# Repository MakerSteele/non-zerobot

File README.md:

# Non-Zerobot

A small 3D-printed FPV robot you drive from your phone's web browser. It streams live video, has RGB headlights, keeps itself driving straight using wheel encoders, and can even *talk* through its drive motors.

It started life as a Raspberry Pi Zero robot — hence the name. Pi Zeros got hard to find, so it now runs happily on a Pi 3B+ too. It's kind of a non-zero bot now.

> **Built on the shoulders of others.** This project is based on Max Kern's **ZeroBot** and **ZeroBot Pro**, and ZDV's **ZeroBot Pro V1** remix. See [CREDITS.md](CREDITS.md).

> 🚧 **Work in progress.** The software works today. The printable parts are in [`models/`](models/). The carrier board on the robot today (Rev F) is in [`hardware/carrier-rev-f/`](hardware/carrier-rev-f/) for reference. It has known faults, so don't order it; the fixed Rev G board will be added once it has been built and tested. Hold off on ordering parts for now.

**Building one?** Go in this order: [parts list](BOM.md) → [assemble it](ASSEMBLY.md) → [install the software](INSTALL.md). Already have a robot? Jump straight to **[INSTALL.md](INSTALL.md)**.

---

## What it does

- **Drive from any phone** — Android or iPhone, nothing to install. Just open a web page.
- **Live video** from the Pi camera, with photo and video recording. **HD VIEW** switches the live picture to full HD for a sharper view or close-up work (more Wi-Fi load while it's on; tested on a Pi 3B+ with the Camera Module 3).
- **RGB headlights** with colour and brightness control.
- **Drives straight on its own** — the encoder motors let it balance left and right wheel speed automatically.
- **Talks through its motors** — hold **TALK** and speak into your phone, or type a sentence under ⚙ → **SOUNDS**, and the robot says it out loud by buzzing its drive motors like a speaker.
- **Built-in self-checks** — buttons to confirm motors and encoders are wired the right way round.
- **Looks after itself** — runs as a background service, restarts if it ever hangs, and shuts down safely on low battery.

## Supported hardware

| Part | Options |
|---|---|
| **Raspberry Pi** | Pi 3B+ (main build), Pi 3B, Pi 3A+, Pi Zero 2 W, Pi Zero W |
| **Camera** | Camera Module 3, OV5647 (cheaper), or the Pi AI Camera (used as a regular camera) |
| **Motors** | Hiwonder geared motors with hall-effect encoders |
| **Motor driver** | TB6612FNG board |
| **Battery** | Two 18650 cells in parallel, with a charger/5 V boost board for the Pi and a 6 V boost for the motors |
| **Battery meter** | ADS1115 ADC board |
| **Headlights** | 10 mm common-anode RGB LEDs |

A carrier circuit board that ties all of this together is in progress and will be added here once the current revision is proven.

## How it got here

| Pi Zero W | Pi Zero 2 W | Out for a drive |
|---|---|---|
|  |  |  |

## Getting started

- 🧾 **[BOM.md](BOM.md)**: every part, with part numbers and a DigiKey order list
- 🔧 **[ASSEMBLY.md](ASSEMBLY.md)**: build the robot step by step (🚧 in progress, not yet tested on a real build)
- 📘 **[Visual assembly manual (PDF)](docs/NonZerobot_Assembly_Manual.pdf)**: the printed chassis put together, step by step, with pictures (🚧 in progress)
- 💾 **[INSTALL.md](INSTALL.md)**: install the software. No Linux experience needed
- 📦 **[Releases](https://github.com/MakerSteele/non-zerobot/releases)**: download just the robot software (`zerobot.zip`)

## Wiring (GPIO, BCM numbering)

| Function | GPIO |
|---|---|
| Left motor forward / backward | 17 / 27 |
| Right motor forward / backward | 22 / 23 |
| Encoders | 5, 13 (6, 19 wired for future use) |
| White headlight | 24 |
| RGB headlight red / green / blue | 12 / 16 / 26 |
| ADS1115 battery sense | I2C (GPIO 2 / 3) |

## Repo layout

```
zerobot/     the robot software - this whole folder goes on the Pi as ~/zerobot
docs/bom/    DigiKey order list and a kit cost calculator
docs/images/ photos
docs/        visual assembly manual (PDF)
models/      3D-printable parts (STL); models/rev-g/ = parts for the Rev G carrier
hardware/    carrier board files (Rev F, for reference: see its known issues)
```

## License

- **Software** (everything in `zerobot/`): [GPL-3.0](LICENSE)
- **Documentation and images**: [CC BY-SA 4.0](LICENSE-DOCS.md)
- **3D models** (everything in `models/`): [CC BY-NC-SA 4.0](models/LICENSE.md) — non-commercial, because the chassis is a remix of ZDV's CC BY-NC-SA design

Found a problem or have an idea? [Open an issue](https://github.com/MakerSteele/non-zerobot/issues).

Follow the build series: **@MakerSteele** on Instagram and TikTok.

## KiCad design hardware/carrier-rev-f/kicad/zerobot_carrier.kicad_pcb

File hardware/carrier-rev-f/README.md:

# Carrier board, Rev F (the board on the robot today)

This is the carrier board the original Non-Zerobot drives on. It's here so you can see exactly what's in the robot.

> ⚠️ **Don't order this board as it is.** It has two wiring faults (below). The robot only works because of hand fixes. **Rev G** fixes both, and its files will be added once a Rev G board has been built and tested.

## Files

| File | What it is |
|---|---|
| `zipme/` | Gerbers for JLCPCB (2 layers, 1.6 mm). **Zip the files inside this folder** and upload that zip |
| `kicad/` | KiCad project (made in KiCad 7; newer versions upgrade it) |
| `zerobot_carrier.step` | 3D model for CAD |
| `zerobot_carrier_schematic.pdf` | Schematic |
| `zerobot_carrier_1to1_fitcheck.pdf` | Print at 100 % and lay the modules on it |
| `scripts/` | The scripts that generate the board |

## Known issues

### 1. Boost footprints are mirrored (both boosts)
The two SX1308 boost footprints ("PI BOOST 5.1V" and "MOTOR BOOST 6.0V") were drawn from the board's label side, so they come out as mirror images. With a boost fitted parts-side up, the battery lands on the boost's **output** pin and nothing reaches its input, so the Pi gets no power.

**Fix on the original robot:**
- **Pi rail:** the Pi boost is removed. The 5 V output of the charger/boost combo board in the shell feeds the Pi side of the **Pi power jumper (JP1)**, with − to the carrier's battery − pad. This skips the rocker switch and the fuse, so pulling JP1 is the Pi's on/off.
- **Motor rail:** a boost set to 6.0 V, wired by hand to match its real pins. Running the motors straight off the battery also works (bridge the battery to the motor side of the **motor power jumper, JP2**), but they're noticeably weaker.

### 2. Motor sockets are reversed
The Hiwonder encoder-motor plug (G, H1, H2, V, M+, M−) lands end-for-end in the left and right motor sockets. With the plug in, the motor driver's output hits the encoder pins and the Pi's 3.3 V hits the motor. The motors don't turn, and **an encoder can be damaged**.

**Fix:** reverse the wire order inside both motor plugs (lift each crimp out of the housing and re-insert it at the other end) before plugging them in.

### 3. Battery + label is misleading
The **+** for the battery is printed nearest the ground pad, and the charger pads have no label. **+ is the square pad** on both.

### 4. Front mounting holes
The front pair of mounting holes sits over the battery-spring install holes. The main lower shell in [`models/`](../../models/) has its standoffs here, so it fits this board. Rev G moves these holes; its lower shell is in [`models/rev-g/`](../../models/rev-g/).

## Tip
The TB6612 motor-driver module goes in one way only: its **PWMA** pin row toward the front (headlight end), its **VM** row toward the rear, with PWMA and VM at the left (Pi-header) end. Fitted the other way round, it shorts the Pi's 3.3 V rail.

## License
Board files are shared under [CC BY-SA 4.0](../../LICENSE-DOCS.md), the same as the docs.

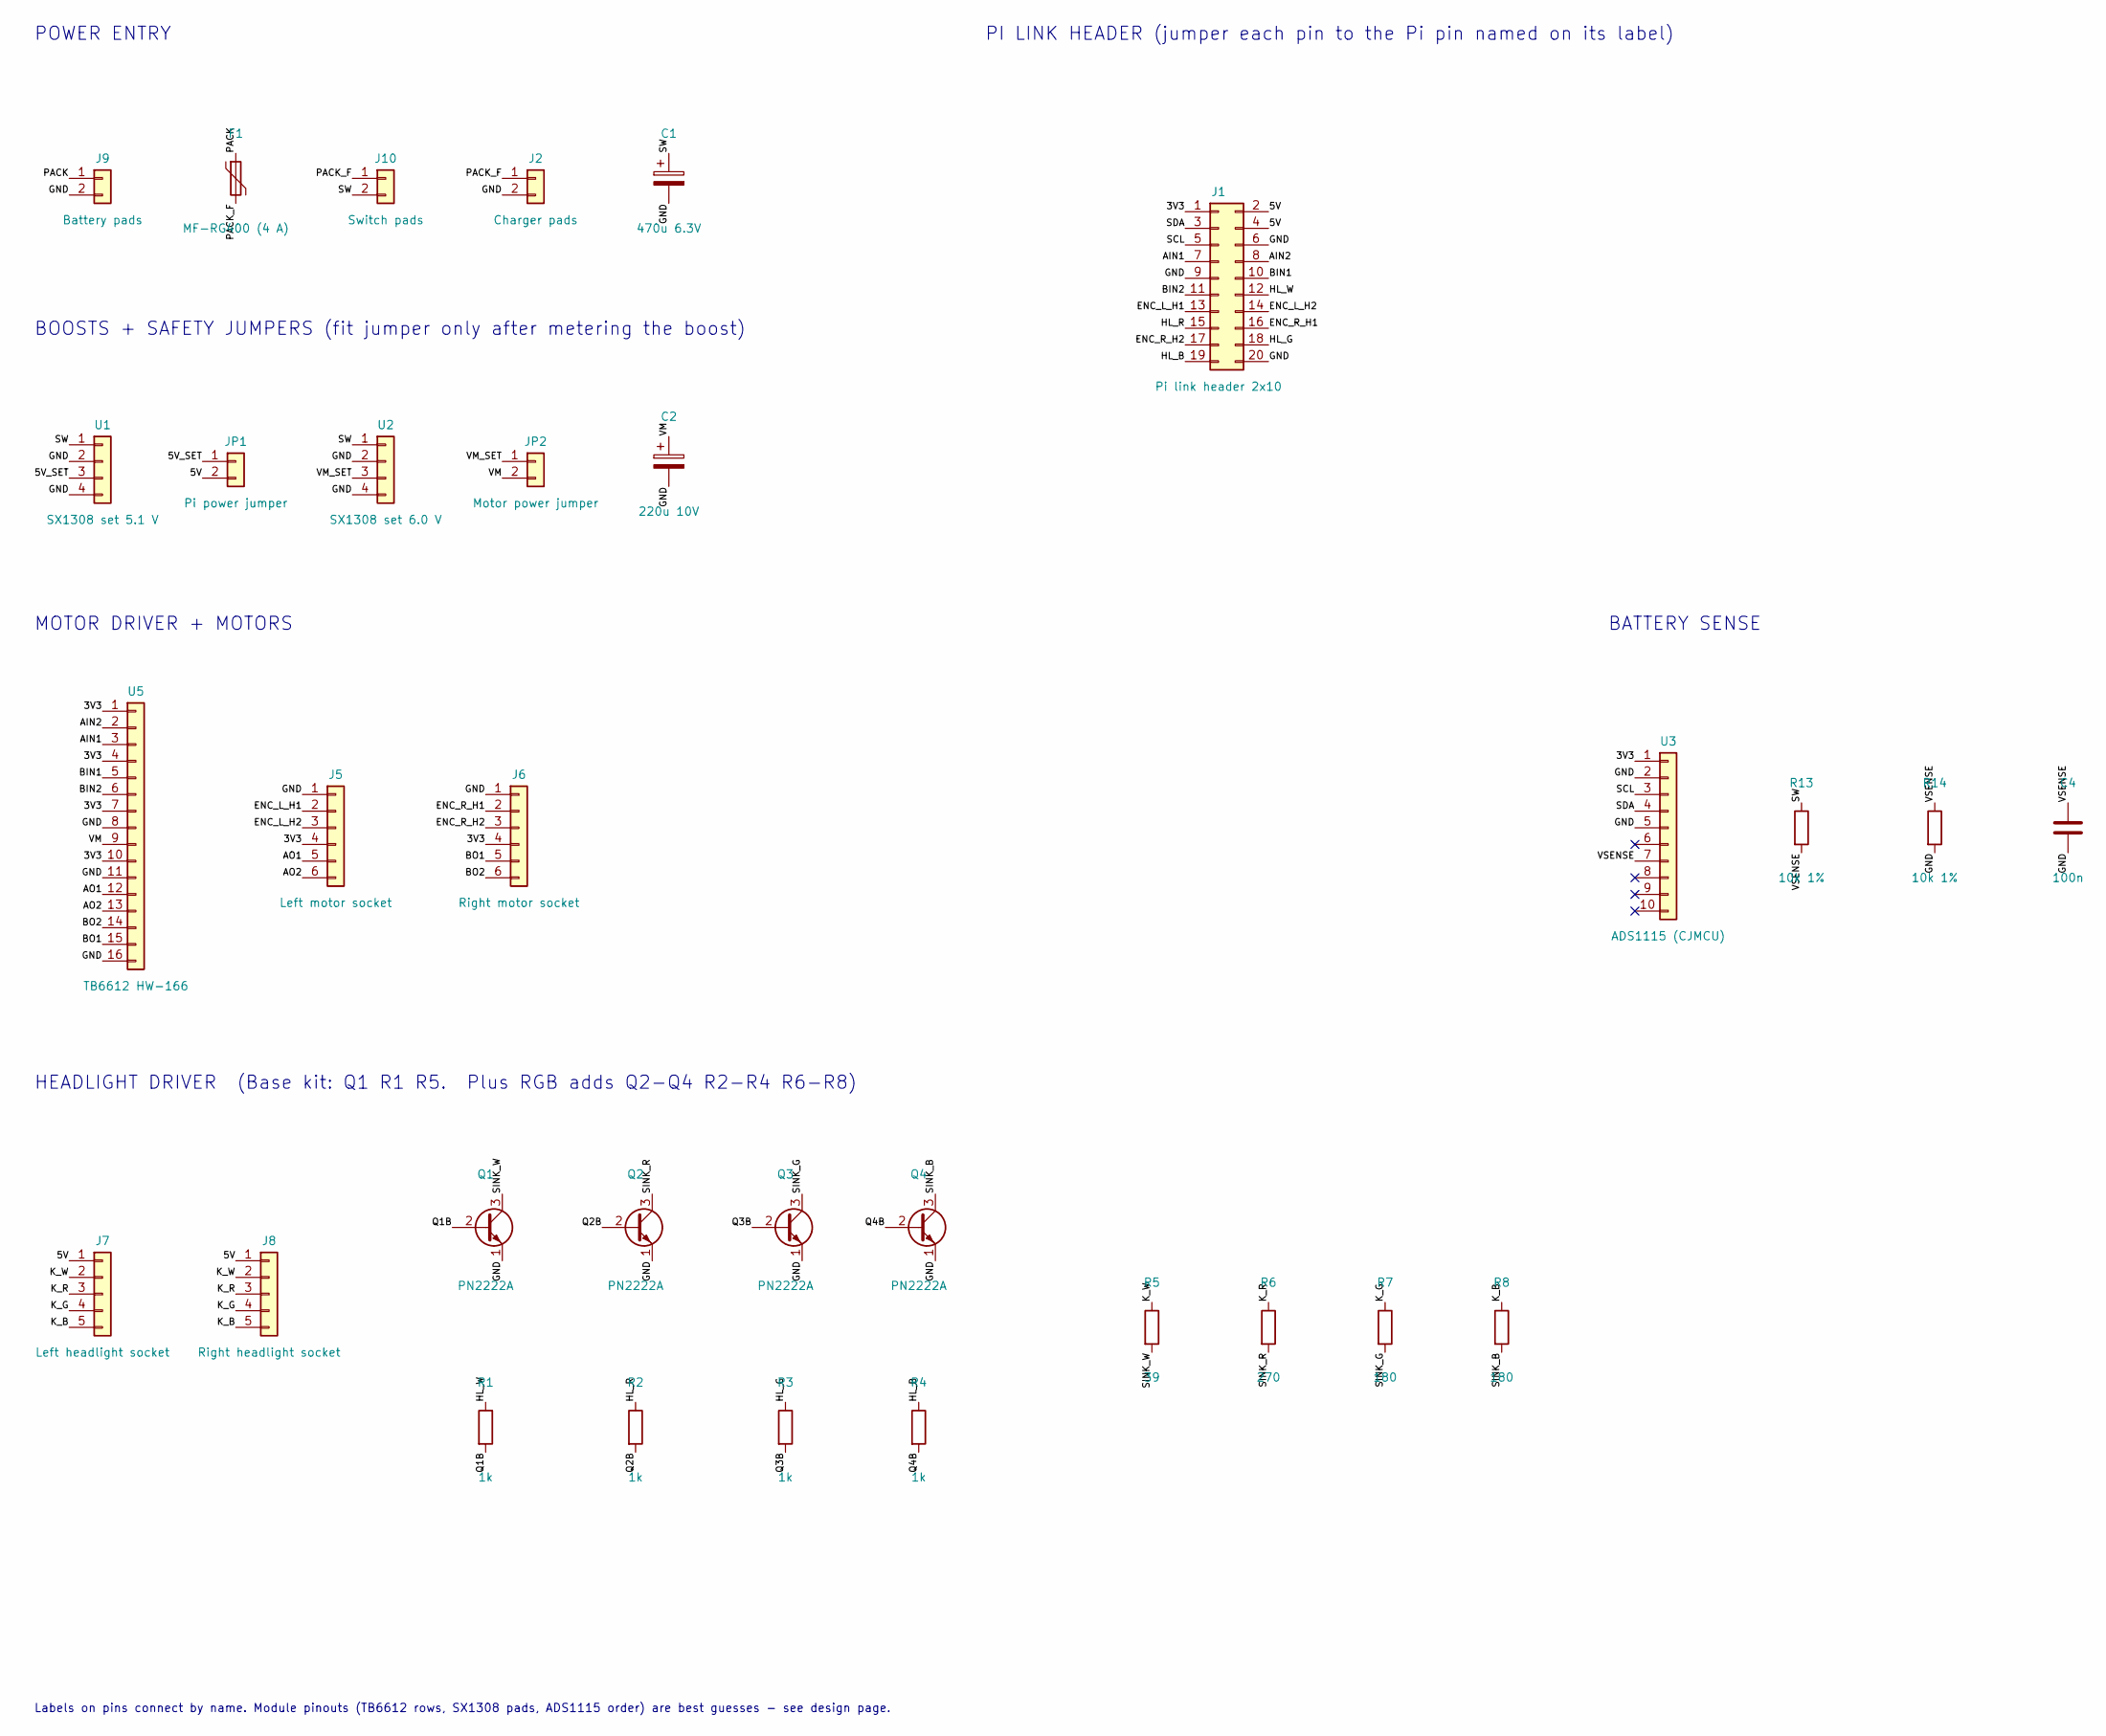
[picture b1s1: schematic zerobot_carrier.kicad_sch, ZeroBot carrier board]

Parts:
C1: 470u 6.3V; CP_Radial_D6.3mm_P2.50mm
C2: 220u 10V; CP_Radial_D6.3mm_P2.50mm
C4: 100n; C_Disc_D3.0mm_W1.6mm_P2.50mm
F1: MF-RG400 (4 A); Fuse_Bourns_MF-RG400
J1: Pi link header 2x10; PinHeader_2x10_P2.54mm_Vertical
J2: Charger pads; SolderWire-0.5sqmm_1x02_P4.8mm_D0.9mm_OD2.3mm
J5: Left motor socket; JST_PH_B6B-PH-K_1x06_P2.00mm_Vertical
J6: Right motor socket; JST_PH_B6B-PH-K_1x06_P2.00mm_Vertical
J7: Left headlight socket; JST_XH_B5B-XH-A_1x05_P2.50mm_Vertical
J8: Right headlight socket; JST_XH_B5B-XH-A_1x05_P2.50mm_Vertical
J9: Battery pads; SolderWire-0.5sqmm_1x02_P4.8mm_D0.9mm_OD2.3mm
J10: Switch pads; SolderWire-0.5sqmm_1x02_P4.8mm_D0.9mm_OD2.3mm
JP1: Pi power jumper; PinHeader_1x02_P2.54mm_Vertical
JP2: Motor power jumper; PinHeader_1x02_P2.54mm_Vertical
Q1, Q2, Q3, Q4: PN2222A; TO-92_Inline
R1, R2, R3, R4: 1k; R_Axial_DIN0207_L6.3mm_D2.5mm_P7.62mm_Horizontal
R5: 39; R_Axial_DIN0207_L6.3mm_D2.5mm_P7.62mm_Horizontal
R6: 270; R_Axial_DIN0207_L6.3mm_D2.5mm_P7.62mm_Horizontal
R7, R8: 180; R_Axial_DIN0207_L6.3mm_D2.5mm_P7.62mm_Horizontal
R13, R14: 10k 1%; R_Axial_DIN0207_L6.3mm_D2.5mm_P7.62mm_Horizontal
U1: SX1308 set 5.1 V; SX1308_Module
U2: SX1308 set 6.0 V; SX1308_Module
U3: ADS1115 (CJMCU); PinSocket_1x10_P2.54mm_Vertical
U5: TB6612 HW-166; TB6612_HW166_Socket

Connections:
3V3: J1.1, J5.4, J6.4, U3.1, U5.1, U5.4, U5.7, U5.10
5V: J1.2, J1.4, J7.1, J8.1, JP1.2
5V_SET: JP1.1, U1.3
AIN1: J1.7, U5.3
AIN2: J1.8, U5.2
AO1: J5.5, U5.12
AO2: J5.6, U5.13
BIN1: J1.10, U5.5
BIN2: J1.11, U5.6
BO1: J6.5, U5.15
BO2: J6.6, U5.14
ENC_L_H1: J1.13, J5.2
ENC_L_H2: J1.14, J5.3
ENC_R_H1: J1.16, J6.2
ENC_R_H2: J1.17, J6.3
GND: C1.2, C2.2, C4.2, J1.6, J1.9, J1.20, J2.2, J5.1, J6.1, J9.2, Q1.1 (E), Q2.1 (E), Q3.1 (E), Q4.1 (E), R14.2, U1.2, U1.4, U2.2, U2.4, U3.2, U3.5, U5.8, U5.11, U5.16
HL_B: J1.19, R4.1
HL_G: J1.18, R3.1
HL_R: J1.15, R2.1
HL_W: J1.12, R1.1
K_B: J7.5, J8.5, R8.1
K_G: J7.4, J8.4, R7.1
K_R: J7.3, J8.3, R6.1
K_W: J7.2, J8.2, R5.1
PACK: F1.1, J9.1
PACK_F: F1.2, J2.1, J10.1
Q1B: Q1.2 (B), R1.2
Q2B: Q2.2 (B), R2.2
Q3B: Q3.2 (B), R3.2
Q4B: Q4.2 (B), R4.2
SCL: J1.5, U3.3
SDA: J1.3, U3.4
SINK_B: Q4.3 (C), R8.2
SINK_G: Q3.3 (C), R7.2
SINK_R: Q2.3 (C), R6.2
SINK_W: Q1.3 (C), R5.2
SW: C1.1, J10.2, R13.1, U1.1, U2.1
VM: C2.1, JP2.2, U5.9
VM_SET: JP2.1, U2.3
VSENSE: C4.1, R13.2, R14.1, U3.7

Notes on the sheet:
POWER ENTRY
BOOSTS + SAFETY JUMPERS (fit jumper only after metering the boost)
MOTOR DRIVER + MOTORS
PI LINK HEADER (jumper each pin to the Pi pin named on its label)
BATTERY SENSE
HEADLIGHT DRIVER (Base kit: Q1 R1 R5. Plus RGB adds Q2-Q4 R2-R4 R6-R8)
Labels on pins connect by name. Module pinouts (TB6612 rows, SX1308 pads, ADS1115 order) are best guesses - see design page.

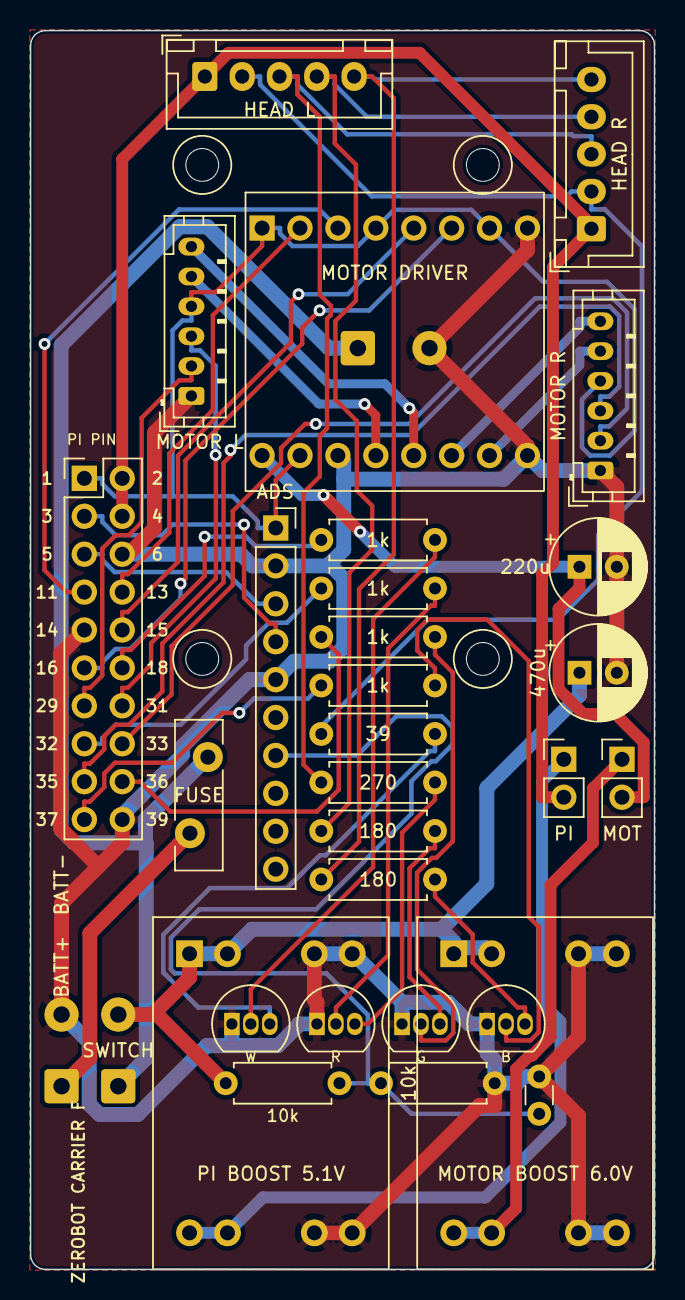
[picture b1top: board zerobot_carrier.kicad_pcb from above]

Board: 2 copper layers, 41.8 x 83.0 mm, 36 parts (0 on the bottom side), 40 nets.

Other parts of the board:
H1, H2, H3, H4: carrier screw (nylon M2 into deck); Hole_M2

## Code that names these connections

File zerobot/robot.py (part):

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WIRING — ZeroBot carrier board (Rev F/G), from 2026-11-05b:
------------------------------------------------------------------
Motor driver TB6612 (on the carrier):
  AIN1 / AIN2  →  GPIO 17 / 27   (left motor forward / backward)
  BIN1 / BIN2  →  GPIO 22 / 23   (right motor forward / backward)
  PWMA, PWMB, STBY tied to 3.3 V on the carrier.

Headlight, white  →  GPIO 24 (physical pin 18). Carrier transistor Q1,
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until the program drives it. (The old GPIO 8 headlight defaulted to pull-UP.)

Battery sense: ADS1115 A0 sits on a 10k/10k divider from the switched pack,
so the pin reads HALF the pack voltage. BATTERY_SCALE = 2.0 below.

Earlier hand-wired builds (L9110S, headlight on GPIO 8, no divider) are not
supported by this build - their notes are in the guide's history.
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
HEADLIGHT_PIN = 24              # carrier Rev F/G white headlight (was GPIO 8 on the hand-wired build)
RGB_PINS = (12, 16, 26)         # red, green, blue (RGB kit only)
BATTERY_SCALE = 2.0             # carrier 10k/10k divider: pack volts = pin volts x 2

try:
    from gpiozero import Motor, PWMLED
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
